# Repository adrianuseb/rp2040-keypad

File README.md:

# RP2040-keypad

## Table of Contents
* [General Info](#general-information)
* [Design](#design)
* [Ordering](#ordering)
* [Flashing Firmware](#flashing-firmware)
* [Case](#case)
* [Assembly](#assembly)

## General Information

This project was made as a learning experience on how to design a MCU-based PCB with minimum components.
It is a 2-key Keypad based on Raspberry RP2040 MCU. It doesn't have any button to enter bootmode, and no LED indicator. Simplicity was the main target.

## Design

This board was designed with KiCad. It is a 4 layer board with signal on the outer layer and power on the inner layer. It has serial wire pin-hole to debugging
and a USB-C header for connection to the host and power. The switches used for the key are mechanical switches and they are connected to GPIO6 and GPIO7. The other end
of the switch connected directly to ground. For programming the BOOT jumper pad must be shorted before connecting the USB.

## Ordering

Ordering and assembly can be done easily at JLCPCB. [Manufacturing_JLCPCB](./Manufacturing_JLCPCB) provide all the necessary files like Gerber, BOM, and components
placement for ordering the board.

## Flashing firmware

Flashing firmware with RP2040 IC is a very simple task. Just short the BOOT jumper while connecting the USB to PC. The board should appear as a mass storage device
on the host PC. Then just copy the [.uf2 file](./rp2040-keypad-1000hz.uf2) there and the board should reset itself. The firmware is written with z and x as the key.

## Case

There is also a simple [case](./case.obj) for 3D printing. The following components are also required for the case:
  - 4 M2 14mm
  - 4 M2 hex nuts

## Assembly

1. Place both of the switch from the top case. It should hold the switches well
2. Align the PCB with the switch. Now should be the right time to solder the switches to the PCB
3. Insert all the hex nuts to the bottom case
4. Place the bottom case aligned with the top case and press until the PCB sits on the bottom case
5. Screw all the M2 screws to secure the case

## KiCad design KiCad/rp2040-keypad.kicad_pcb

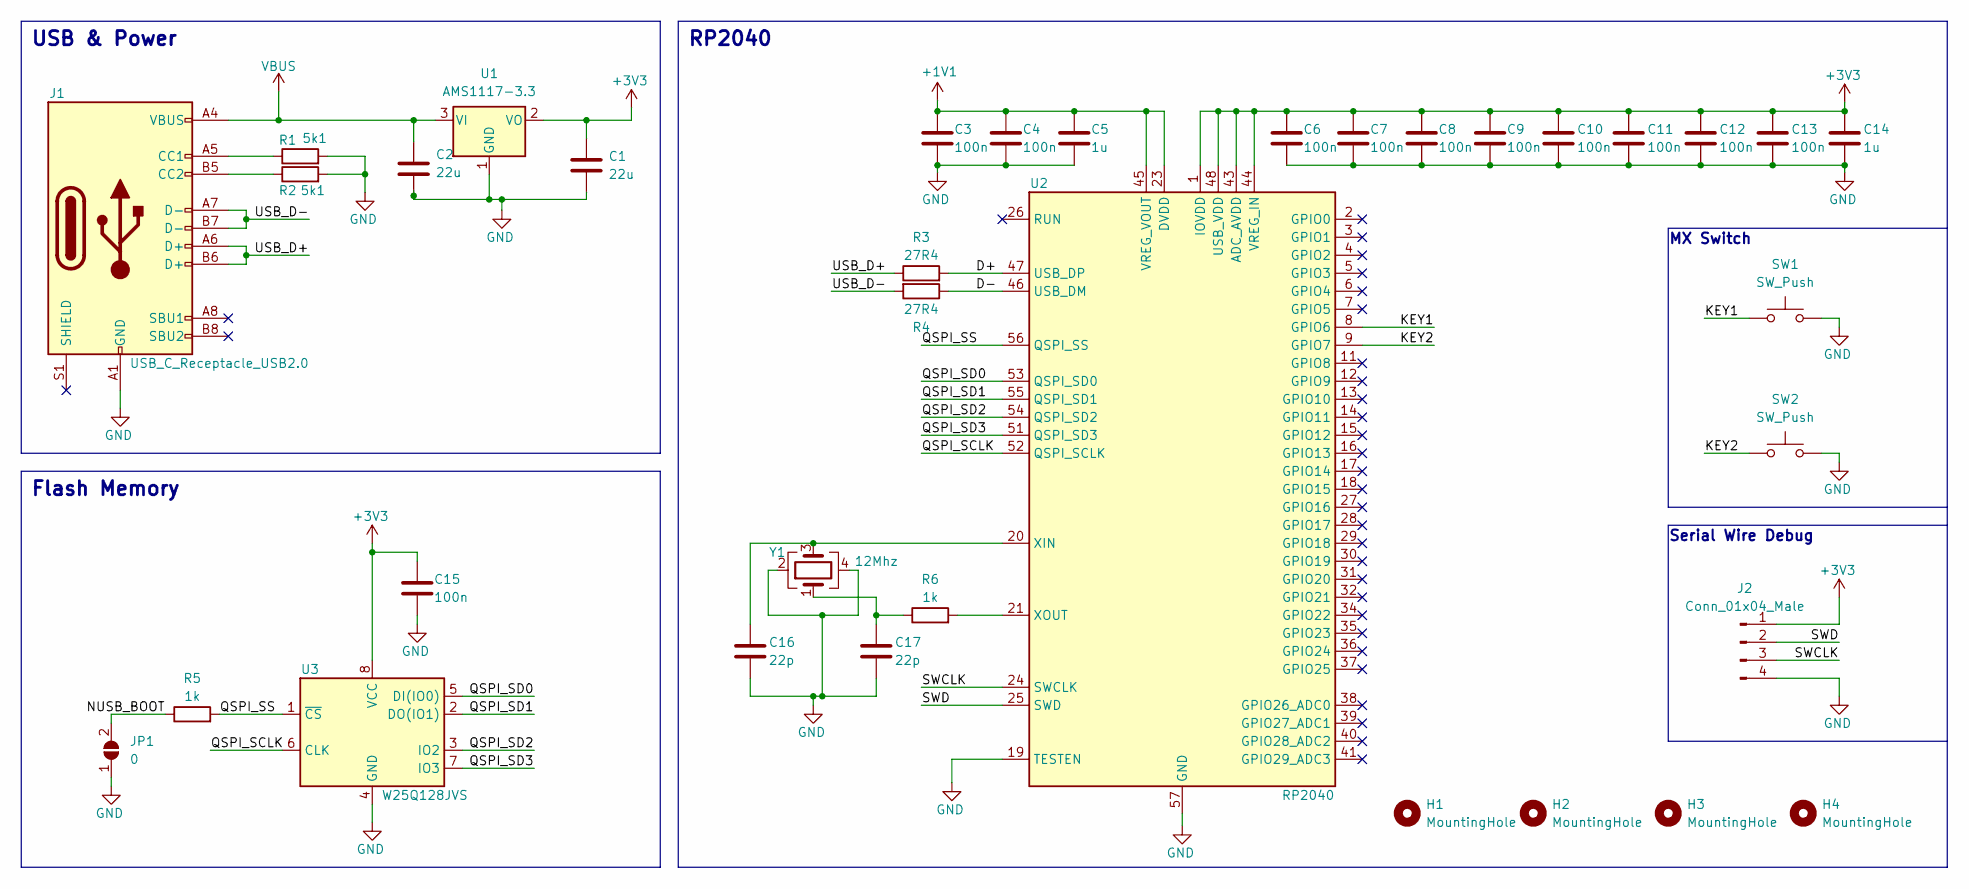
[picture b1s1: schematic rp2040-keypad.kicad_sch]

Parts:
C1, C2: 22u; C_0603_1608Metric; LCSC C59461
C3, C4, C6, C7, C8, C9, C10, C11, C12, C13, C15: 100n; C_0402_1005Metric; LCSC C1525
C5, C14: 1u; C_0402_1005Metric; LCSC C52923
C16, C17: 22p; C_0402_1005Metric; LCSC C1555
H1, H2, H3, H4: MountingHole; MountingHole_2.2mm_M2_DIN965
J1: USB_C_Receptacle_USB2.0; USB_C_Receptacle_HRO_TYPE-C-31-M-12; LCSC C165948
J2: Conn_01x04_Male; SolderWire-0.1sqmm_1x04_P3.6mm_D0.4mm_OD1mm
JP1: 0; SolderJumper-2_P1.3mm_Open_Pad1.0x1.5mm
R1, R2: 5k1; R_0402_1005Metric; LCSC C25905
R3, R4: 27R4; R_0402_1005Metric; LCSC C26971
R5, R6: 1k; R_0402_1005Metric; LCSC C11702
SW1, SW2: SW_Push; SW_Cherry_MX_PCB_1.00u
U1: AMS1117-3.3; SOT-223-3_TabPin2; LCSC C6186
U2: RP2040; QFN-56-1EP_7x7mm_P0.4mm_EP3.2x3.2mm; LCSC C2040
U3: W25Q128JVS; SOIC-8_5.23x5.23mm_P1.27mm; LCSC C97521
Y1: 12Mhz; Crystal_SMD_3225-4Pin_3.2x2.5mm; LCSC C9002

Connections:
+1V1: C3.1, C4.1, C5.1, U2.23 (DVDD), U2.45 (VREG_VOUT), U2.50 (DVDD)
+3V3: C1.1, C6.1, C7.1, C8.1, C9.1, C10.1, C11.1, C12.1, C13.1, C14.1, C15.1, J2.1, U1.2 (VO), U2.1 (IOVDD), U2.10 (IOVDD), U2.22 (IOVDD), U2.33 (IOVDD), U2.42 (IOVDD), U2.43 (ADC_AVDD), U2.44 (VREG_IN), U2.48 (USB_VDD), U2.49 (IOVDD), U3.8 (VCC)
/D+: R3.2, U2.47 (USB_DP)
/D-: R4.1, U2.46 (USB_DM)
/KEY1: SW1.1, U2.8 (GPIO6)
/KEY2: SW2.1, U2.9 (GPIO7)
/NUSB_BOOT: JP1.2 (B), R5.1
/QSPI_SCLK: U2.52 (QSPI_SCLK), U3.6 (CLK)
/QSPI_SD0: U2.53 (QSPI_SD0), U3.5 (DI(IO0))
/QSPI_SD1: U2.55 (QSPI_SD1), U3.2 (DO(IO1))
/QSPI_SD2: U2.54 (QSPI_SD2), U3.3 (IO2)
/QSPI_SD3: U2.51 (QSPI_SD3), U3.7 (IO3)
/QSPI_SS: R5.2, U2.56 (QSPI_SS), U3.1 (~CS)
/SWCLK: J2.3, U2.24 (SWCLK)
/SWD: J2.2, U2.25 (SWD)
/USB_D+: J1.A6 (D+), J1.B6 (D+), R3.1
/USB_D-: J1.A7 (D-), J1.B7 (D-), R4.2
GND: C1.2, C2.2, C3.2, C4.2, C5.2, C6.2, C7.2, C8.2, C9.2, C10.2, C11.2, C12.2, C13.2, C14.2, C15.2, C16.2, C17.2, J1.A1 (GND), J1.A12 (GND), J1.B1 (GND), J1.B12 (GND), J2.4, JP1.1 (A), R1.2, R2.2, SW1.2, SW2.2, U1.1 (GND), U2.19 (TESTEN), U2.57 (GND), U3.4 (GND), Y1.2, Y1.4
unnamed: C16.1, U2.20 (XIN), Y1.3
unnamed: C17.1, R6.1, Y1.1
unnamed: J1.A5 (CC1), R1.1
unnamed: J1.B5 (CC2), R2.1
unnamed: R6.2, U2.21 (XOUT)
VBUS: C2.1, J1.A4 (VBUS), J1.A9 (VBUS), J1.B4 (VBUS), J1.B9 (VBUS), U1.3 (VI)

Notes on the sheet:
MX Switch
Flash Memory
RP2040
Serial Wire Debug
USB & Power

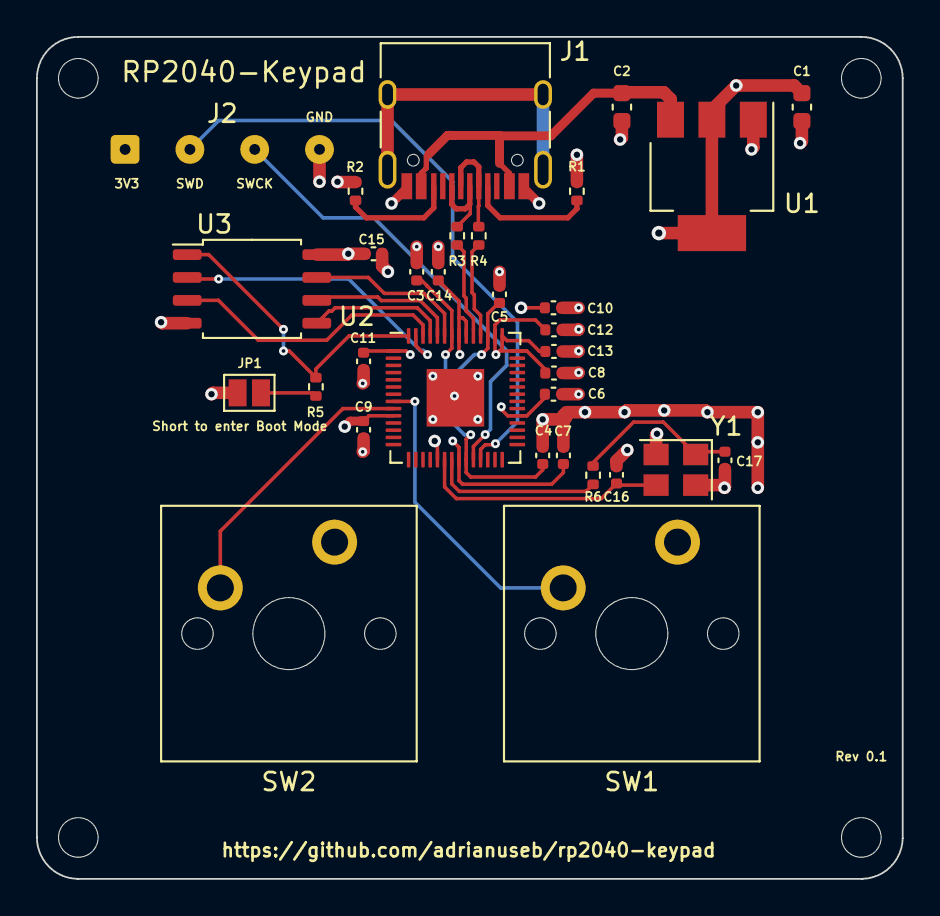
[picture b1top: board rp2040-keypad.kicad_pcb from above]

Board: 4 copper layers, 48.1 x 46.8 mm, 36 parts (0 on the bottom side), 24 nets.

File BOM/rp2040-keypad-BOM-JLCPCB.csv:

Comment,Designator,Footprint,LCSC
"22u","C1,C2","Capacitor_SMD:C_0603_1608Metric","C59461"
"22p","C16,C17","Capacitor_SMD:C_0402_1005Metric","C1555"
"100n","C3,C4,C6,C7,C8,C9,C10,C11,C12,C13,C15","Capacitor_SMD:C_0402_1005Metric","C1525"
"1u","C5,C14","Capacitor_SMD:C_0402_1005Metric","C52923"
"USB_C_Receptacle_USB2.0","J1","Connector_USB:USB_C_Receptacle_HRO_TYPE-C-31-M-12","C165948"
"5k1","R1,R2","Resistor_SMD:R_0402_1005Metric","C25905"
"27R4","R3,R4","Resistor_SMD:R_0402_1005Metric","C26971"
"1k","R5,R6","Resistor_SMD:R_0402_1005Metric","C11702"
"AMS1117-3.3","U1","Package_TO_SOT_SMD:SOT-223-3_TabPin2","C6186"
"RP2040","U2","Package_DFN_QFN:QFN-56-1EP_7x7mm_P0.4mm_EP3.2x3.2mm","C2040"
"W25Q128JVS","U3","Package_SO:SOIC-8_5.23x5.23mm_P1.27mm","C97521"
"12Mhz","Y1","Crystal:Crystal_SMD_3225-4Pin_3.2x2.5mm","C9002"

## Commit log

2022-09-11 Initial KiCad project
2022-09-13 Finish schematic and footprint assignment
2022-09-13 First draft completed ready to review
2022-09-14 Rev 0.1 ready for production
2022-09-15 Update silkscreen position and information
2022-09-15 Update gerber files
2022-09-15 Added missing 3D Library
2022-09-15 Updated gerber files
2022-09-15 Reposition and resize some ground vias
2022-09-15 Added 3D file
2022-09-15 Fix component ID R3&R4 for JLCPCB
2022-09-28 Add firmware for 2 keys keypad
2022-09-30 Add 3d case file
